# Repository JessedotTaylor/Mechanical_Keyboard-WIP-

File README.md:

These are the work in progress files for the design of a custom mechanical keyboard

Currently working on a POC numpad to test spacing, microcontroller choice, LED wiring and control, and other features.

Current working version for numpad - 'discipad-ESP32'
PCB files were designed in KiCad

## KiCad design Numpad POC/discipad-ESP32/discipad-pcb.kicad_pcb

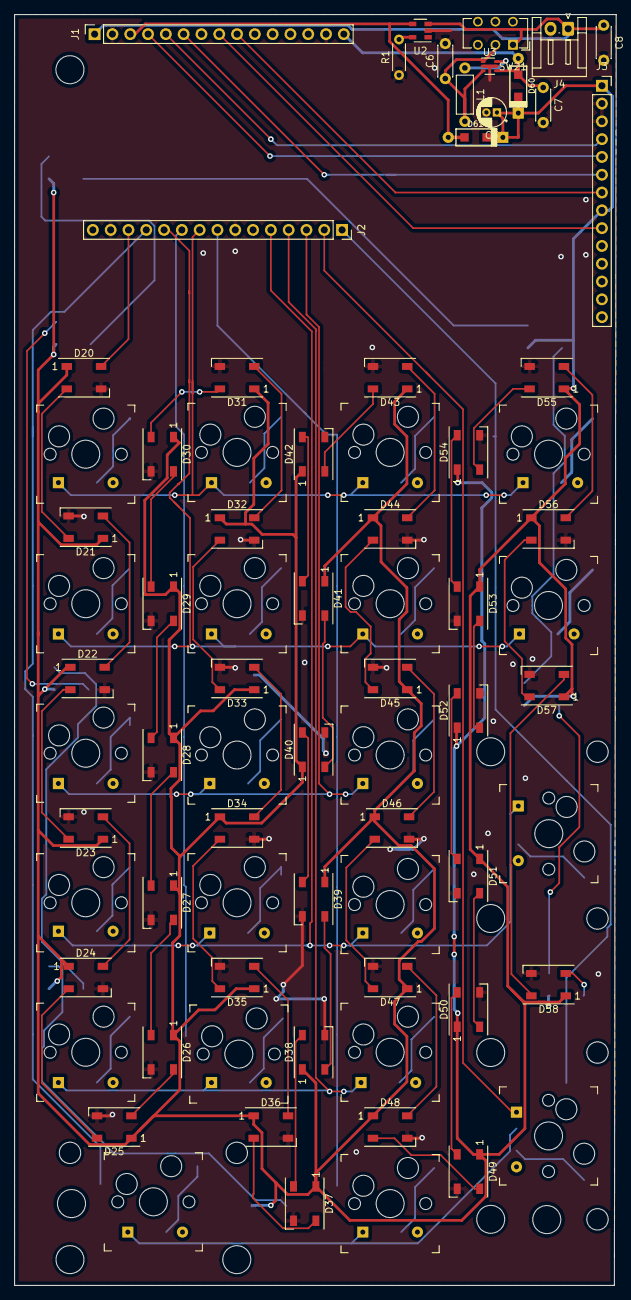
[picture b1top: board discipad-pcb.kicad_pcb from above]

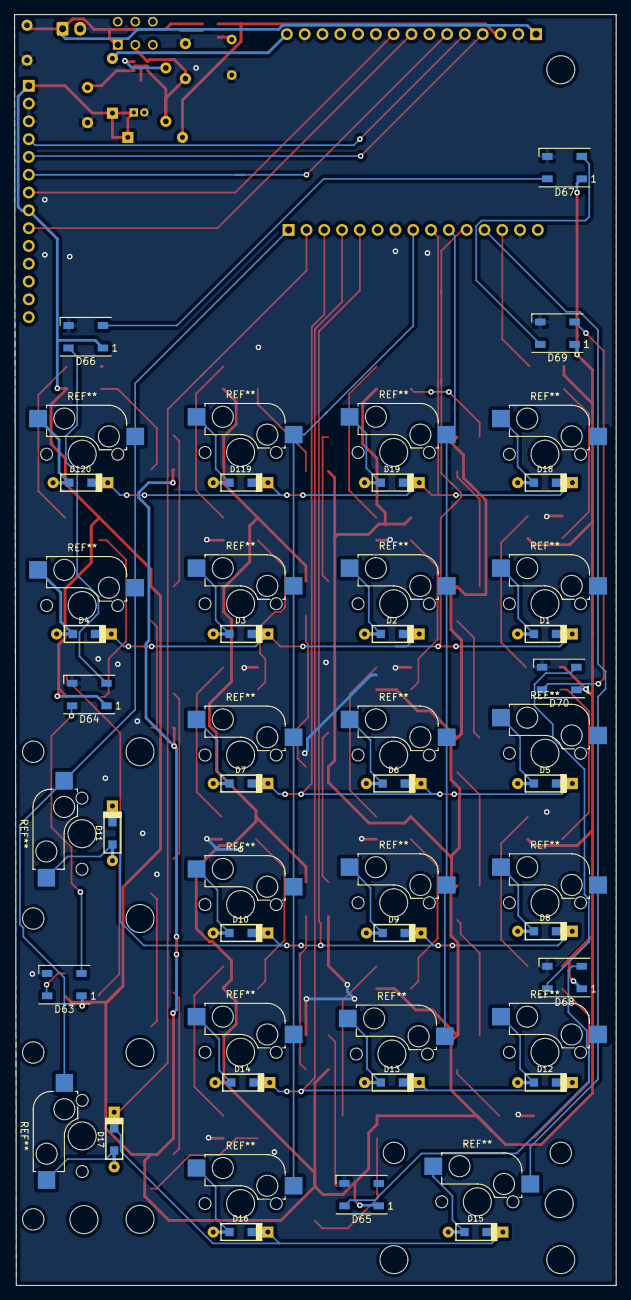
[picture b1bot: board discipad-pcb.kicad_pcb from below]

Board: 2 copper layers, 85.9 x 181.4 mm, 83 parts (29 on the bottom side), 66 nets.

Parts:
C3: 4.7u; CP_Radial_D4.0mm_P1.50mm
C6: 1u; C_Disc_D4.3mm_W1.9mm_P5.00mm
C7: 22uF / 6.3V; C_Disc_D4.3mm_W1.9mm_P5.00mm
C8: 4.7u; C_Disc_D4.3mm_W1.9mm_P5.00mm
D1, D2, D3, D4, D5, D6, D7, D8, D9, D10, D11, D12, D13, D14, D15, D16, D17, D18, D19, D119, D120: D_SOD123_axial
D20, D21, D22, D23, D24, D25, D26, D27, D28, D29, D30, D31, D32, D33, D34, D35, D36, D37, D38, D39, D40, D41, D42, D43, D44, D45, D46, D47, D48, D49, D50, D51, D52, D53, D54, D55, D56, D57, D58, D63, D64, D65, D66, D67, D68, D69, D70: WS2812B; LED_WS2812B_PLCC4_5.0x5.0mm_P3.2mm
D60, D61: 1N5820; D_SOD123_axial
J1: 1x15 RH UD NodeMCU; PinSocket_1x15_P2.54mm_Vertical
J2: 1x15 LH UD NodeMCU; PinSocket_1x15_P2.54mm_Vertical
J3: LCD Header 1x14; PinSocket_1x14_P2.54mm_Vertical
J4: 3.7V Bat 1x2; JST_EH_S2B-EH_1x02_P2.50mm_Horizontal
L1: 10u; L_Axial_L5.3mm_D2.2mm_P7.62mm_Horizontal_Vishay_IM-1
R1: 2K; R_Axial_DIN0204_L3.6mm_D1.6mm_P5.08mm_Horizontal
SW21: ON; SW_CuK_JS202011AQN_DPDT_Angled
U2: MCP73831-2-OT; SOT-23-5
U3: LTC3525-5; SOT-363_SC-70-6

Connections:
5VREG: C7.1, D60.2, J1.15, U3.4
5VUSB: D61.2, J1.3, U2.4
+5V: C3.1, D20.1, D21.1, D22.1, D23.1, D24.1, D25.1, D26.1, D27.1, D28.1, D29.1, D30.1, D31.1, D32.1, D33.1, D34.1, D35.1, D36.1, D37.1, D38.1, D39.1, D40.1, D41.1, D42.1, D43.1, D44.1, D45.1, D46.1, D47.1, D48.1, D49.1, D50.1, D51.1, D52.1, D53.1, D54.1, D55.1, D56.1, D57.1, D58.1, D60.1, D61.1, D63.1, D64.1, D65.1, D66.1, D67.1, D68.1, D69.1, D70.1, J3.1, J3.8
GND: C3.2, C6.2, C7.2, C8.2, D20.3, D21.3, D22.3, D23.3, D24.3, D25.3, D26.3, D27.3, D28.3, D29.3, D30.3, D31.3, D32.3, D33.3, D34.3, D35.3, D36.3, D37.3, D38.3, D39.3, D40.3, D41.3, D42.3, D43.3, D44.3, D45.3, D46.3, D47.3, D48.3, D49.3, D50.3, D51.3, D52.3, D53.3, D54.3, D55.3, D56.3, D57.3, D58.3, D63.3, D64.3, D65.3, D66.3, D67.3, D68.3, D69.3, D70.3, J1.2, J1.10, J1.14, J2.7, J2.14, J3.2, J3.3, J4.2, R1.1, U2.2, U3.2, U3.5
LCD_RS: J1.4, J3.5
LCD_RST: J1.5, J3.4
LEDin: D20.4, J2.13
MISO: J1.8, J3.9
MOSI: J1.6, J3.6
unnamed: C6.1, L1.2, SW21.2, U3.1, U3.3
unnamed: D20.2, D21.4
unnamed: D21.2, D22.4
unnamed: D22.2, D23.4
unnamed: D23.2, D24.4
unnamed: D24.2, D25.4
unnamed: D25.2, D26.4
unnamed: D26.2, D27.4
unnamed: D27.2, D28.4
unnamed: D28.2, D29.4
unnamed: D29.2, D30.4
unnamed: D30.2, D31.4
unnamed: D31.2, D32.4
unnamed: D32.2, D33.4
unnamed: D33.2, D34.4
unnamed: D34.2, D35.4
unnamed: D35.2, D36.4
unnamed: D36.2, D37.4
unnamed: D37.2, D38.4
unnamed: D38.2, D39.4
unnamed: D39.2, D40.4
unnamed: D40.2, D41.4
unnamed: D41.2, D42.4
unnamed: D42.2, D43.4
unnamed: D43.2, D44.4
unnamed: D44.2, D45.4
unnamed: D45.2, D46.4
unnamed: D46.2, D47.4
unnamed: D47.2, D48.4
unnamed: D48.2, D49.4
unnamed: D49.2, D50.4
unnamed: D50.2, D51.4
unnamed: D51.2, D52.4
unnamed: D52.2, D53.4
unnamed: D53.2, D54.4
unnamed: D54.2, D55.4
unnamed: D55.2, D56.4
unnamed: D56.2, D57.4
unnamed: D57.2, D58.4
unnamed: D63.2, D64.4
unnamed: D64.2, D66.4
unnamed: D65.4, D68.2
unnamed: D66.2, D67.4
unnamed: D67.2, D69.4
unnamed: D68.4, D70.2
unnamed: D69.2, D70.4
unnamed: L1.1, U3.6
unnamed: R1.2, U2.5
SCK: J1.9, J3.7
UNDERGLOW: D58.2, D63.4
VBAT: C8.1, J1.1, J4.1, SW21.1, U2.3
row0: D1.1, D2.1, D3.1, D4.1, J2.11
row1: D5.1, D6.1, D7.1, J2.3
row2: D8.1, D9.1, D10.1, D11.1, J2.5
row3: D12.1, D13.1, D14.1, J2.4
row4: D15.1, D16.1, D17.1, J2.2
row5: D18.1, D19.1, D119.1, D120.1, J2.9
